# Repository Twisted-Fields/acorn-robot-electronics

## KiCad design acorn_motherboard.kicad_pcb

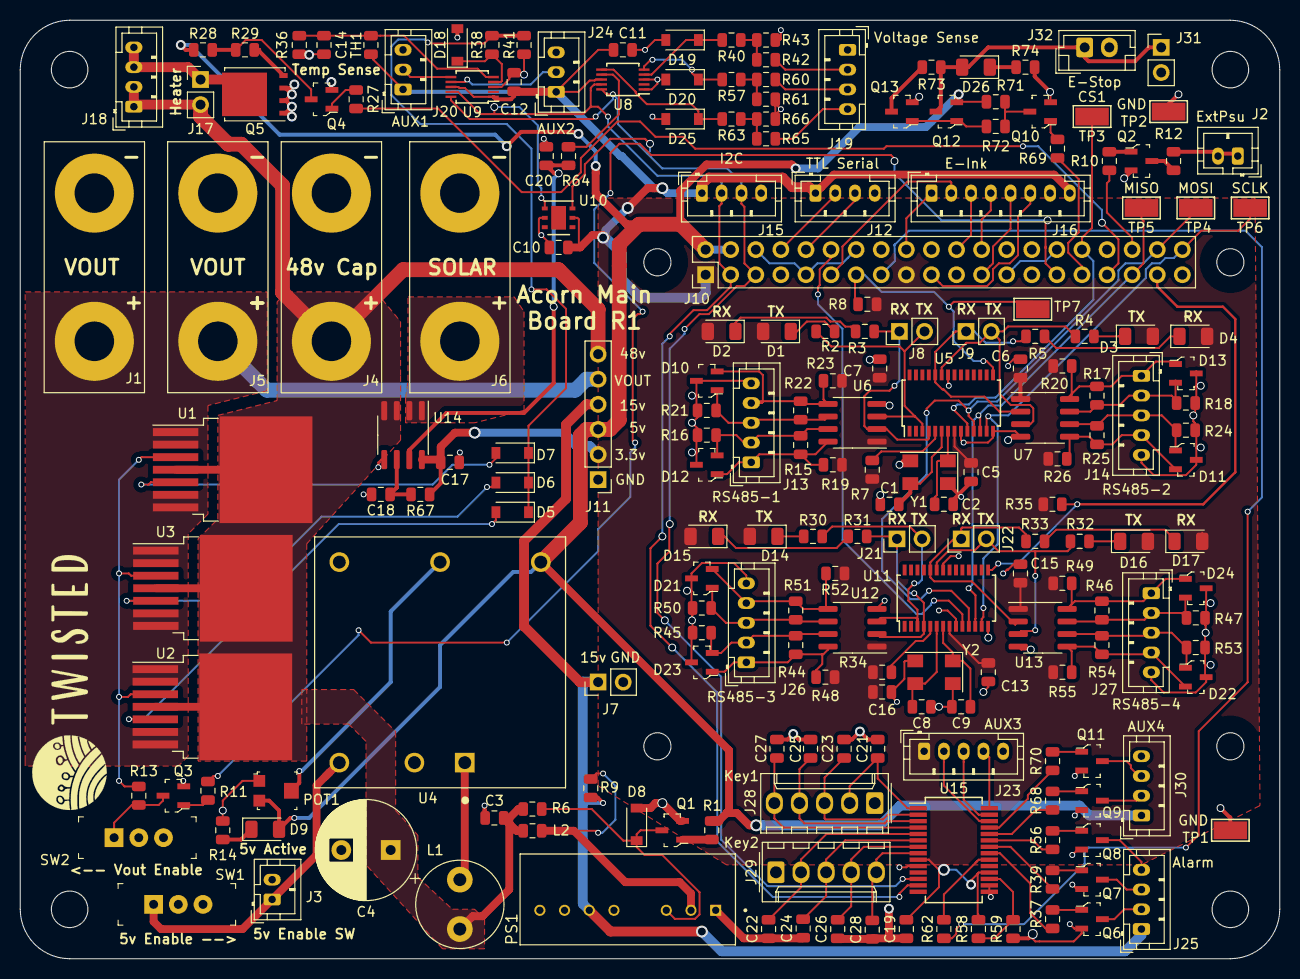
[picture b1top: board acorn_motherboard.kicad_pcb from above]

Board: 2 copper layers, 127.5 x 95.0 mm, 208 parts (0 on the bottom side), 138 nets.

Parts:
C1, C2, C8, C9: 18pF; C_0805_2012Metric
C3: 1uF 100v; C_0805_2012Metric
C4: CP; CP_Radial_D10.0mm_P5.00mm
C5, C6, C7, C10, C11, C12, C13, C14, C15, C16, C17, C19, C21, C22, C23, C24, C25, C26, C27, C28: 0.1uF; C_0805_2012Metric
C18: 1nF; C_0805_2012Metric
C20: 0.15uF; C_0805_2012Metric
D1, D2, D3, D4, D9, D14, D15, D16, D17, D26: LED; LED_1206_3216Metric
D5, D6, D7: D; D_SOD-123
D8: 12v Zener; D_SOD-123
D10, D11, D12, D13, D21, D22, D23, D24: CDSOT23-SM712; SOT-23-3
D18, D19, D20, D25: 3.3v Zener; D_SOD-123
H1, H2, H3, H4: MountingHole; MountingHole_3.7mm
J1, J4, J5, J6: Conn_01x02; BigWirePads
J2, J3: Conn_01x02; JST_PH_B2B-PH-K_1x02_P2.00mm_Vertical
J7, J8, J9, J17, J21, J22, J31: Conn_01x02; PinHeader_1x02_P2.54mm_Vertical
J10: RPi_GPIO; PinHeader_2x20_P2.54mm_Vertical
J11: Conn_01x06; PinHeader_1x06_P2.54mm_Vertical
J12, J15, J18, J19, J25, J30: Conn_01x04; JST_PH_B4B-PH-K_1x04_P2.00mm_Vertical
J13, J14, J23, J26, J27: Conn_01x05; JST_PH_B5B-PH-K_1x05_P2.00mm_Vertical
J16: Conn_01x08; JST_PH_B8B-PH-K_1x08_P2.00mm_Vertical
J20, J24: Conn_01x03; JST_PH_B3B-PH-K_1x03_P2.00mm_Vertical
J28, J29: Conn_01x05; Molex_KK-254_AE-6410-05A_1x05_P2.54mm_Vertical
J32: Conn_01x02; JST_EH_B2B-EH-A_1x02_P2.50mm_Vertical
L1: L; L_Radial_D8.7mm_P5.00mm_Fastron_07HCP
L2: 10uH; L_0805_2012Metric
POT1: TC33X-2-103E; Trimpot_3.8mmx3.6mm_TC33X-2-103E
PS1: SPBW06F-12; CONV_SPBW06F-12
Q1, Q2, Q3, Q4, Q6, Q7, Q8, Q9, Q10, Q11, Q13: 2N7002; SOT-23-3
Q5: FDMS8050; TDSON-8-1
Q12: AO3401A; SOT-23-3
R1, R10, R11, R12, R27, R29, R37, R39, R56, R68, R69, R70, R72, R73: 100R; R_0805_2012Metric
R2, R3, R4, R5, R30, R31, R32, R33: 500R; R_0805_2012Metric
R6, R28, R36, R38, R40, R57, R63, R64: 1k; R_0805_2012Metric
R7, R34, R42, R43, R59, R60, R61, R62, R65, R66: 10K; R_0805_2012Metric
R8, R35: 1K; R_0805_2012Metric
R9: 150pF; R_0805_2012Metric
R13, R41: 330R; R_0805_2012Metric
R14, R74: 220R; R_0805_2012Metric
R15, R17, R22, R25, R44, R46, R51, R54: 130R; R_0805_2012Metric
R16, R18, R19, R20, R21, R23, R24, R26, R45, R47, R48, R49, R50, R52, R53, R55: 750R; R_0805_2012Metric
R58: DNS; R_0805_2012Metric
R67: DNS for ACS725 / 0R for ACS722; R_0805_2012Metric
R71: 10k; R_0805_2012Metric
SW1, SW2: SW_SPDT; Switch_Slide_11.6x4mm_EG1218
TH1: Thermistor; R_0805_2012Metric
TP1, TP2, TP3, TP4, TP5, TP6, TP7: TestPoint; TestPoint_Keystone_5015_Micro-Minature
U1, U2, U3: BTS50085-1TMA; TO-263-7_TabPin4
U4: PDQ30-Q48-S5-D; CONV_PDQ30-Q48-S5-D
U5, U11: SC16IS752; TSSOP-28_4.4x9.7mm_P0.65mm
U6, U7, U12, U13: THVD1451D; SOIC-8_3.9x4.9mm_P1.27mm
U8, U9: ADS1115IDGS; TSSOP-10_3x3mm_P0.5mm
U10: HDC1080; Texas_PWSON-N6
U14: ACS725xLCTR-10AU; SOIC-8_3.9x4.9mm_P1.27mm
U15: MCP23017_SS; SSOP-28_5.3x10.2mm_P0.65mm
Y1, Y2: Crystal_GND24; Crystal_SMD_Abracon_ABM3C-4Pin_5.0x3.2mm

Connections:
15V_REMOTE: D8.1, PS1.3, Q1.3, R6.2
18VMAXIN: J19.2, R42.2
36VMAXIN: J19.3, R60.2
54VMAXIN: J19.4, R65.2
+3V3: C5.2, C6.1, C7.1, C10.1, C11.2, C12.2, C13.2, C15.1, C16.1, C17.2, C19.2, D1.2, D2.2, D3.2, D4.2, D14.2, D15.2, D16.2, D17.2, J10.1, J10.17, J11.2, J12.1, J15.1, J16.8, J20.1, J23.1, J24.1, R7.2, R8.2, R19.2, R20.2, R23.1, R26.1, R34.2, R35.2, R48.2, R49.2, R52.1, R55.1, R58.2, R67.1, TH1.1, U5.8, U6.1, U7.1, U8.8, U9.1, U9.8, U10.5, U11.8, U12.1, U13.1, U14.8, U15.9, U15.18
+5V: D9.2, J10.2, J10.4, J11.3, J30.1, POT1.3, Q12.2, R1.2, R28.1, R71.1, U4.3
+15V: J7.1, J11.4, J25.1, PS1.6, R9.1
+48V: C3.1, C4.1, J4.2, J11.6, J17.2, J18.1, J18.2, L1.2, L2.2, R6.1, U1.4, U2.4, U3.4, U14.3, U14.4
A1: D19.1, R40.2, U8.4
A2: D20.1, R57.2, U8.5
A3: D25.1, R63.2, U8.6
A4: R64.1, U8.7
A5: D18.1, R38.2, U9.4
A6: C14.1, R36.2, TH1.2, U9.5
A7: J20.2, U9.6
A8: J24.2, U9.7
CS1: J10.12, U11.10
CS2: J10.32, TP3.1, U5.10
EPD_BUSY: J10.18, J16.1
EPD_CS: J10.24, J16.4
EPD_DC: J10.22, J16.3
EPD_DIN: J10.19, J16.6
EPD_RESET: J10.11, J16.2
EPD_SCK: J10.23, J16.5
ESTOP: D26.2, J31.1, J32.1, Q12.3, R73.2
ESTOP_FET: J10.31, R69.1
EXT_PSU_ENABLE: J2.1, J2.2, R12.2
EXT_PSU_FET: J10.36, R10.1
GND: C1.1, C2.2, C3.2, C4.2, C5.1, C6.2, C7.2, C8.1, C9.2, C10.2, C11.1, C12.1, C13.1, C14.2, C15.2, C16.2, C17.1, C18.1, C19.1, C20.2, C21.1, C22.1, C23.1, C24.1, C25.1, C26.1, C27.1, C28.1, D8.2, D10.3, D11.3, D12.3, D13.3, D18.2, D19.2, D20.2, D21.3, D22.3, D23.3, D24.3, D25.2, J1.1, J3.2, J4.1, J5.1, J6.1, J7.2, J10.6, J10.9, J10.14, J10.20, J10.25, J10.30, J10.34, J10.39, J11.1, J12.4, J13.5, J14.5, J15.4, J16.7, J19.1, J20.3, J23.5, J24.3, J26.5, J27.5, J28.1, J29.1, J30.4, J31.2, J32.2, POT1.1, PS1.1, PS1.7, Q1.2, Q2.2, Q3.2, Q4.2, Q5.1, Q5.2, Q5.3, Q6.2, Q7.2, Q8.2, Q9.2, Q10.2, Q11.2, Q13.2, R14.2, R16.1, R18.1, R21.1, R24.1, R36.1, R41.2, R43.1, R45.1, R47.1, R50.1, R53.1, R59.1, R61.1, R66.1, R74.2, SW1.2, SW2.2, TP1.1, TP2.1, U4.2, U4.5, U5.9, U5.14, U5.22, U6.4, U7.4, U8.1, U8.3, U9.3, U10.2, U11.9, U11.14, U11.22, U12.4, U13.4, U14.5, U15.10, U15.15, U15.16, Y1.2, Y1.4, Y2.2, Y2.4
GP0: C21.2, J28.2, U15.1
GP1: C23.2, J28.3, U15.2
GP2: C25.2, J28.4, U15.3
GP3: C27.2, J28.5, U15.4
GP4: C22.2, J29.2, U15.5
GP5: C24.2, J29.3, U15.6
GP6: C26.2, J29.4, U15.7
GP7: C28.2, J29.5, U15.8
GP8: R37.1, U15.21
GP9: R39.1, U15.22
GP10: R56.1, U15.23
GP11: R68.1, U15.24
GP12: R70.1, U15.25
GP13: J23.2, U15.26
GP14: J23.3, U15.27
GP15: J23.4, U15.28
GPIO_INT: J10.15, R62.1
IRQ1: J10.37, R35.1, U11.15
IRQ2: J10.13, R8.1, TP7.1, U5.15
MISO: J10.35, TP5.1, U5.12, U11.12
MOSI: J10.38, TP4.1, U5.11, U11.11
unnamed: C1.2, U5.6, Y1.3
unnamed: C2.1, U5.7, Y1.1
unnamed: C8.2, U11.6, Y2.3
unnamed: C9.1, U11.7, Y2.1
unnamed: C18.2, R67.2, U14.6
unnamed: C20.1, R64.2, U14.7
unnamed: D1.1, R2.1
unnamed: D2.1, R3.1
unnamed: D3.1, R4.1
unnamed: D4.1, R5.1
unnamed: D5.2, U2.5
unnamed: D6.2, U3.5
unnamed: D7.2, U1.5
unnamed: D9.1, R14.1
unnamed: D10.1, J13.3, R21.2, R22.2, U6.6
unnamed: D10.2, J13.4, R22.1, R23.2, U6.5
unnamed: D11.1, J14.3, R24.2, R25.2, U7.6
unnamed: D11.2, J14.4, R25.1, R26.2, U7.5
unnamed: D12.1, J13.1, R15.2, R19.1, U6.8
unnamed: D12.2, J13.2, R15.1, R16.2, U6.7
unnamed: D13.1, J14.1, R17.2, R20.1, U7.8
unnamed: D13.2, J14.2, R17.1, R18.2, U7.7
unnamed: D14.1, R30.1
unnamed: D15.1, R31.1
unnamed: D16.1, R32.1
unnamed: D17.1, R33.1
unnamed: D21.1, J26.3, R50.2, R51.2, U12.6
unnamed: D21.2, J26.4, R51.1, R52.2, U12.5
unnamed: D22.1, J27.3, R53.2, R54.2, U13.6
unnamed: D22.2, J27.4, R54.1, R55.2, U13.5
unnamed: D23.1, J26.1, R44.2, R48.1, U12.8
unnamed: D23.2, J26.2, R44.1, R45.2, U12.7
unnamed: D24.1, J27.1, R46.2, R49.1, U13.8
unnamed: D24.2, J27.2, R46.1, R47.2, U13.7
unnamed: D26.1, R74.1
unnamed: J3.1, SW1.1, U4.6
unnamed: J17.1, J18.3, J18.4, Q5.5
unnamed: J25.2, Q6.3
unnamed: J25.3, Q7.3
unnamed: J25.4, Q8.3
unnamed: J30.2, Q9.3
unnamed: J30.3, Q11.3
unnamed: L1.1, U4.1
unnamed: L2.1, PS1.2, R9.2
unnamed: POT1.2, U4.4
unnamed: Q1.1, R1.1
unnamed: Q2.1, R10.2
unnamed: Q2.3, R12.1
unnamed: Q3.1, R11.2
unnamed: Q3.3, R13.1, SW2.1
unnamed: Q4.1, R27.2
unnamed: Q4.3, R28.2, R29.1
unnamed: Q5.4, R29.2
unnamed: Q6.1, R37.2
unnamed: Q7.1, R39.2
unnamed: Q8.1, R56.2
unnamed: Q9.1, R68.2
unnamed: Q10.1, R69.2
unnamed: Q10.3, R71.2, R72.2
unnamed: Q11.1, R70.2
unnamed: Q12.1, Q13.1, R72.1
unnamed: Q13.3, R73.1
unnamed: R7.1, U5.5
unnamed: R34.1, U11.5
unnamed: R40.1, R42.1, R43.2
unnamed: R57.1, R60.1, R61.2
unnamed: R58.1, R59.2, U15.17
unnamed: R62.2, U15.20
unnamed: R63.1, R65.1, R66.2
PWM_HEATER: J10.33, R27.1
RX: J10.10, J12.3
RX1: J21.1, R31.2, U11.4, U12.2
RX2: J22.1, R33.2, U11.24, U13.2
RX3: J8.1, R3.2, U5.4, U6.2
RX4: J9.1, R5.2, U5.24, U7.2
SCL: J10.5, J15.3, U8.10, U9.10, U10.6, U15.12
SCLK: J10.40, TP6.1, U5.13, U11.13
SDA: J10.3, J15.2, U8.9, U9.9, U10.1, U15.13
SOLARIN: J6.2, U14.1, U14.2
TX: J10.8, J12.2
TX1: J21.2, R30.2, U11.3, U12.3
TX2: J22.2, R32.2, U11.23, U13.3
TX3: J8.2, R2.2, U5.3, U6.3
TX4: J9.2, R4.2, U5.23, U7.3
VOUT: J1.2, J5.2, J11.5, U1.1, U1.2, U1.6, U1.7, U2.1, U2.2, U2.6, U2.7, U3.1, U3.2, U3.6, U3.7
VOUT_FET: J10.29, R11.1
VOUT_ISENSE: D5.1, D6.1, D7.1, R38.1, R41.1
|VOUT_ENABLE|: R13.2, U1.3, U2.3, U3.3

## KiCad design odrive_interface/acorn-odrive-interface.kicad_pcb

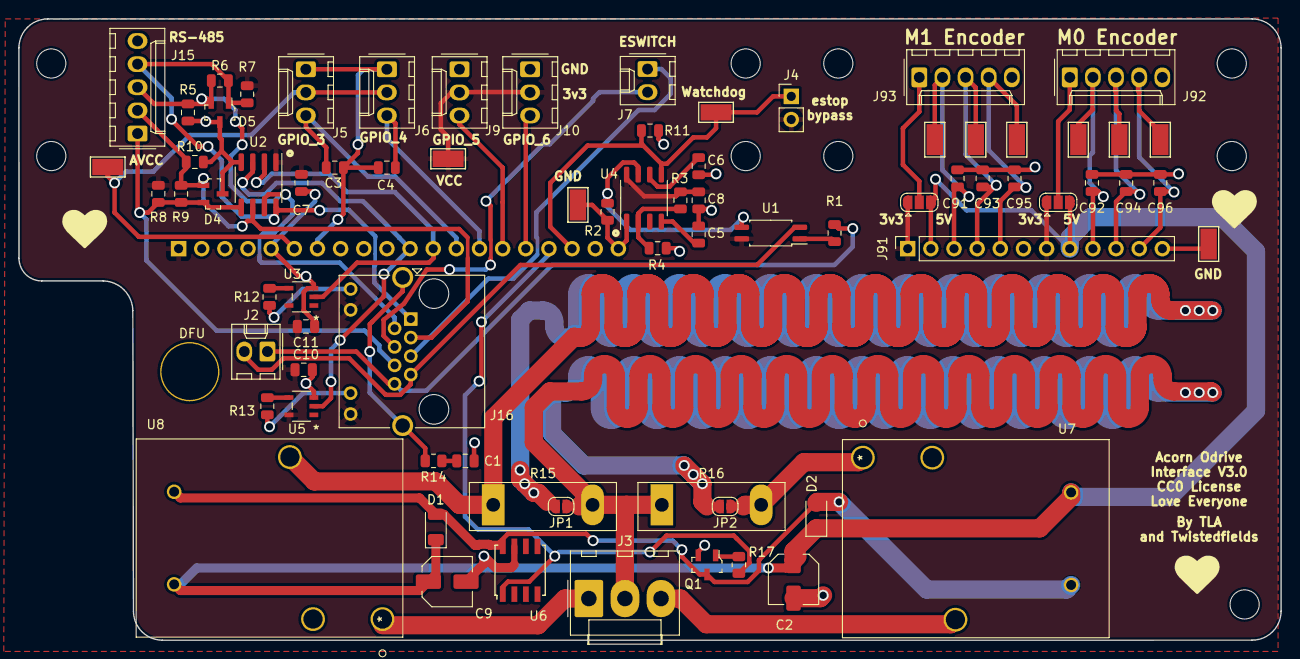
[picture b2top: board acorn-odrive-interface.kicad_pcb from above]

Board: 2 copper layers, 138.5 x 68.2 mm, 86 parts (1 on the bottom side), 47 nets.

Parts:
C1, C7, C8, C10, C11: 0.1uF; C_0805_2012Metric
C2, C9: 10uF; C_Elec_5x5.4
C3, C4: DNP; C_0805_2012Metric
C5, C6: 3900pF NP0; C_0805_2012Metric
C91, C92, C93, C94, C95, C96: 47pF; C_0805_2012Metric
D1, D2: D; D_1206_3216Metric
D4, D5: CDSOT23-SM712; SOT-23-3
H1, H2, H3, H4, H5, H91, H92, H93, H94: MountingHole; MountingHole_3.2mm_M3
H9: MountingHole; MountingHole_6.4mm_M6
J1: Conn_01x20_Male; PinHeader_1x20_P2.54mm_Vertical
J2: DNP; Molex_KK-254_AE-6410-02A_1x02_P2.54mm_Vertical
J3: DNP; Molex_KK-396_A-41791-0003_1x03_P3.96mm_Vertical
J4: Conn_01x02; PinHeader_1x02_P2.54mm_Vertical
J5, J6, J9, J10: Conn_01x03; Molex_KK-254_AE-6410-03A_1x03_P2.54mm_Vertical
J7: Conn_01x02; Molex_KK-254_AE-6410-02A_1x02_P2.54mm_Vertical
J15: Conn_01x05; Molex_KK-254_AE-6410-05A_1x05_P2.54mm_Vertical
J16: RJ45_LED_Shielded; RJ45_Amphenol_RJHSE538X
J91: Conn_01x12_Female; PinSocket_1x12_P2.54mm_Vertical
J92, J93: Conn_01x05_Male; Molex_KK-254_AE-6410-05A_1x05_P2.54mm_Vertical
JP1, JP2: SolderJumper_2_Open; SolderJumper-2_P1.3mm_Open_RoundedPad1.0x1.5mm
JP91, JP92: SolderJumper_3_Bridged12; SolderJumper-3_P1.3mm_Open_RoundedPad1.0x1.5mm
Q1: DNP; SOT-23-3
R1: 220R; R_0805_2012Metric
R2, R11: 10k; R_0805_2012Metric
R3, R4: 1M; R_0805_2012Metric
R5, R7, R8, R10: 750R; R_0805_2012Metric
R6, R9: 130R; R_0805_2012Metric
R12, R13, R14: 470R; R_0805_2012Metric
R15, R16: DNP; TO-247-2_Vertical
R17: 100R; R_0805_2012Metric
TP1, TP2, TP4, TP5, TP91, TP92, TP93, TP94, TP95, TP96, TP97: TestPoint; TestPoint_Keystone_5015_Micro-Minature
U1: PS2805A-1-A; SOP-4_4.4x2.6mm_P1.27mm
U2: THVD1451D; SOIC-8_3.9x4.9mm_P1.27mm
U3, U5: buffer; SN74LVC1G07QDCKTQ1
U4: UCC2946D; SO-8_3.9x4.9mm_P1.27mm
U6: BV1LC105FJ-C; SOJ-8_6x4mm_P1.27mm
U7, U8: 1558667-1

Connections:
3v3: C7.1, C8.1, C10.1, C11.1, J1.1, J4.2, J9.2, J10.2, J16.10, J16.12, J91.1, J91.7, JP91.1 (A), JP92.1 (A), R3.2, R7.2, R8.1, TP1.1, U1.4, U2.1 (VCC), U3.5 (VCC), U4.8 (VDD), U5.5 (VCC)
5V: C2.1, C9.1, D1.1 (K), D2.1 (K), J91.2, J91.8, JP91.3 (B), JP92.3 (B), U7.4, U8.4
/Enc1PosV: J93.1, JP92.2 (C)
AGND: C3.2, C4.2, J1.7, J5.1, J6.1
AVCC: J1.6, J5.2, J6.2, TP5.1
COIL_DRIVE: D1.2 (A), D2.2 (A), Q1.3 (D), U6.8 (OUT1), U7.5, U8.5
E1: J2.1, J16.8, R1.1
E2: J2.2, J16.7, U1.2
E_SWITCH1: J7.1, J16.5
E_SWITCH2: J7.2, J16.4
Enc0A: C92.1, J91.9, J92.2, TP95.1
Enc0B: C94.1, J91.10, J92.3, TP96.1
Enc0Z: C96.1, J91.11, J92.4, TP97.1
Enc1A: C91.1, J91.3, J93.2, TP92.1
Enc1B: C93.1, J91.4, J93.3, TP93.1
Enc1Z: C95.1, J91.5, J93.4, TP94.1
GND: C1.1, C2.2, C5.2, C6.2, C7.2, C8.2, C9.2, C10.2, C11.2, C91.2, C92.2, C93.2, C94.2, C95.2, C96.2, D4.3 (Output), D5.3 (Output), J1.2, J1.5, J1.19, J1.20, J9.1, J10.1, J15.5, J91.6, J91.12, J92.5, J93.5, Q1.2 (S), R2.2, R4.1, R5.1, R10.1, R11.2, TP4.1, TP91.1, U2.4 (GND), U3.3 (GND), U4.1 (GND), U5.3 (GND), U6.7 (GND)
GPIO_1: J1.11, U2.3 (D), U5.2 (A)
GPIO_2: J1.12, U2.2 (R), U3.2 (A)
GPIO_3: C3.1, J1.13, J5.3
GPIO_4: C4.1, J1.14, J6.3
GPIO_5: J1.15, J9.3
GPIO_6: J1.16, J10.3
GPIO_7: J1.17, R17.2, U6.1 (IN)
GPIO_8: J1.18, J4.1, R11.1, TP2.1, U4.5 (*WDO)
unnamed: C1.2, R14.2
unnamed: C5.1, U4.4 (RP)
unnamed: C6.1, U4.6 (WP)
unnamed: D4.1 (Input), J15.2, J16.3, R9.2, R10.2, U2.6 (Z)
unnamed: D4.2 (Input), J15.1, J16.6, R8.2, R9.1, U2.5 (Y)
unnamed: D5.1 (Input), J15.4, J16.1, R6.2, R7.1, U2.8 (A)
unnamed: D5.2 (Input), J15.3, J16.2, R5.2, R6.1, U2.7 (B)
unnamed: J3.1, U8.1
unnamed: J3.2, JP1.1 (A), JP2.2 (B), R15.2, R16.1
unnamed: J3.3, U7.3
unnamed: J16.9, R12.2
unnamed: J16.11, R13.2
unnamed: J16.SH, R14.1
unnamed: J92.1, JP91.2 (C)
unnamed: JP1.2 (B), R15.1, U8.3
unnamed: JP2.1 (A), R16.2, U7.1
unnamed: Q1.1 (G), R17.1
unnamed: R1.2, U1.1
unnamed: R3.1, R4.2, U4.2 (RTH)
WDI: R2.1, U1.3, U4.7 (WDI)
led_buffer_rx: R12.1, U3.4 (Y)
led_buffer_tx: R13.1, U5.4 (Y)

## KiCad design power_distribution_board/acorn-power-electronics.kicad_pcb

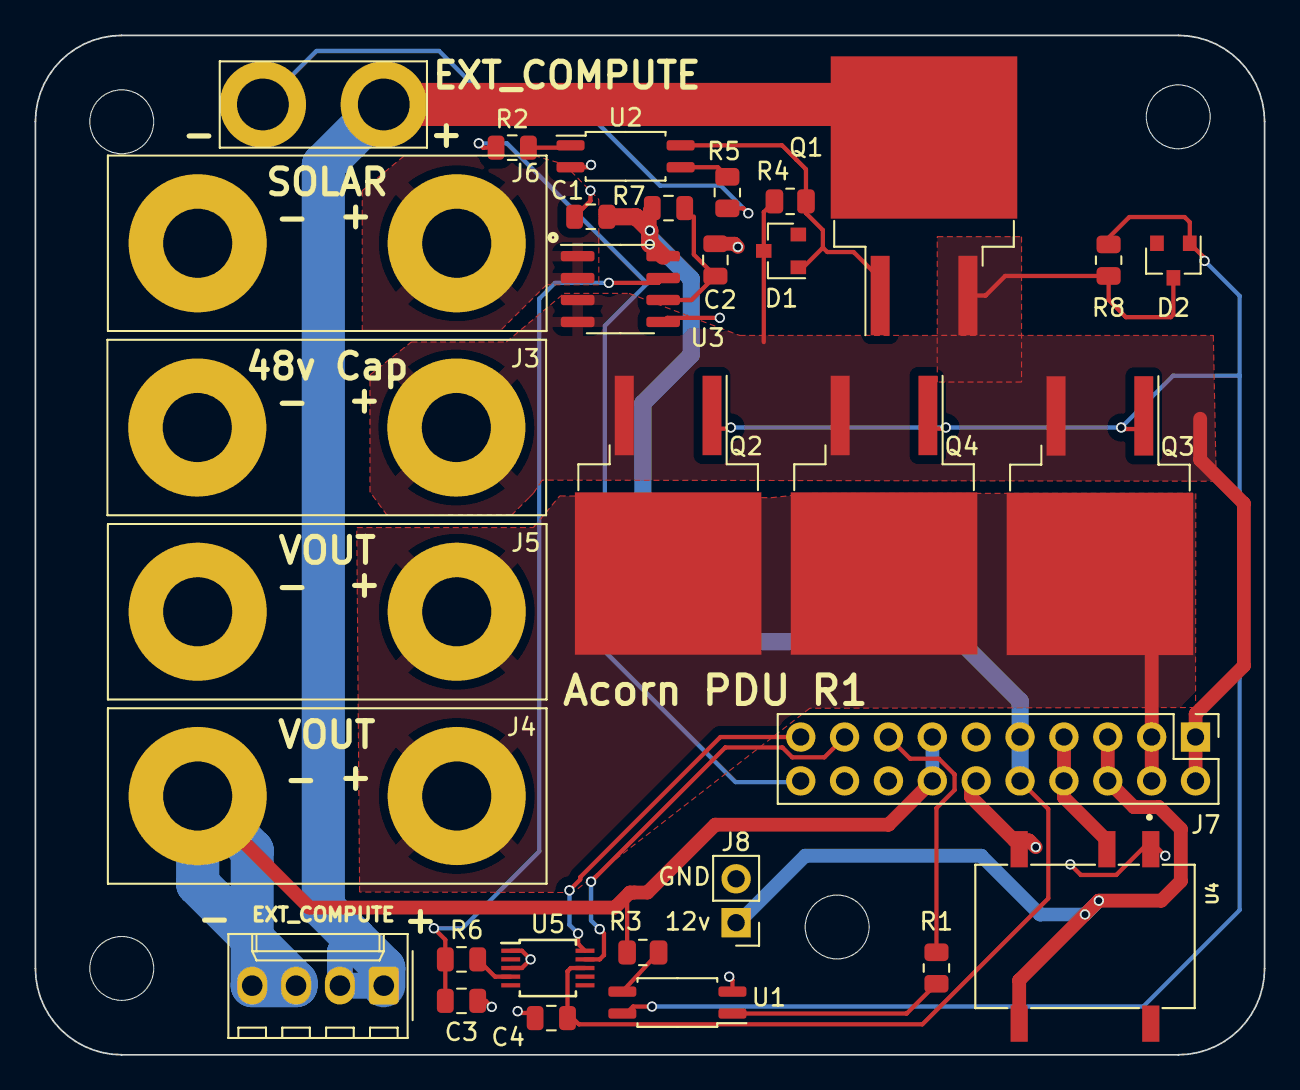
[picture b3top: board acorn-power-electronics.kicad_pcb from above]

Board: 2 copper layers, 71.2 x 59.0 mm, 35 parts (0 on the bottom side), 22 nets.

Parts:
C1, C4: 0.1uF; C_0805_2012Metric
C2: 1000pF; C_0805_2012Metric
C3: 0.15uF; C_0805_2012Metric
D1, D2: BZX84Cxx; D_SOT-23_ANK
H1, H2, H3, H4: MountingHole; MountingHole_3.7mm
J1: Conn_01x04; Molex_KK-254_AE-6410-04A_1x04_P2.54mm_Vertical
J2: Conn_01x02; medium_big_pads
J3, J4, J5, J6: Conn_01x02; BigWirePads
J7: Conn_02x10_Counter_Clockwise; PinHeader_2x10_P2.54mm_Vertical
J8: Conn_01x02; PinHeader_1x02_P2.54mm_Vertical
Q1, Q2, Q3, Q4: IXTA96P085T-TRL; TO-263-2-pad4
R1, R2: 330R; R_0805_2012Metric
R3, R5: 200; R_0805_2012Metric
R4, R6, R8: 1k; R_0805_2012Metric
R7: DNS for ACS725 / 0R for ACS722; R_0805_2012Metric
U1, U2: ACPL-214-500E; SOP-4_4.4x2.6mm_P1.27mm
U3: ACS725xLCTR-10AU; SOIC-8_3.9x4.9mm_P1.27mm
U4: PDS1-S5-S12-M-TR; CONV_PDS1-S3-S3-M
U5: ADS1115IDGS; TSSOP-10_3x3mm_P0.5mm

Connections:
+3V3: C1.2, C4.2, J7.9, J7.10, R7.1, U3.8 (VCC), U5.8 (VDD)
+5V: J7.7, J7.8, U4.2 (VIN)
+12V: J7.5, J7.6, J8.1, U4.5 (+VO)
+48V: D1.1 (K), D2.1 (K), J3.2, J7.1, J7.2, Q1.3 (S), Q2.3 (S), Q3.3 (S), Q4.3 (S), R4.2, R8.2, U3.3 (IP-), U3.4 (IP-)
A1: R6.1, U5.4 (AIN0)
EXT_PSU_FET: J7.20, R2.1
GND: C1.1, C2.1, C3.2, C4.1, J7.11, J7.12, J8.2, U1.2, U2.2, U3.5 (GND), U4.1 (GND), U4.4 (0V), U5.1 (ADDR), U5.3 (GND)
GNDPWR: J1.3, J1.4, J2.2, J3.1, J4.1, J5.1, J6.1, J7.13, J7.14, R3.1, R5.1
unnamed: C2.2, R7.2, U3.6 (FILTER)
unnamed: C3.1, R6.2, U3.7 (VIOUT)
unnamed: D1.2 (A), Q1.1 (G), R4.1, U2.4
unnamed: R1.2, U1.1
unnamed: R2.2, U2.1
unnamed: R3.2, U1.3
unnamed: R5.2, U2.3
SCL: J7.19, U5.10 (SCL)
SDA: J7.17, U5.9 (SDA)
SOLARIN: J6.2, U3.1 (IP+), U3.2 (IP+)
VOUT: J4.2, J5.2, J7.3, J7.4, Q2.4 (D), Q3.4 (D), Q4.4 (D)
VOUT_ENABLE: J7.15, R1.1
VOUT_EXT_COMPUTE: J1.1, J1.2, J2.1, Q1.4 (D)
VOUT_FET: D2.2 (A), Q2.1 (G), Q3.1 (G), Q4.1 (G), R8.1, U1.4

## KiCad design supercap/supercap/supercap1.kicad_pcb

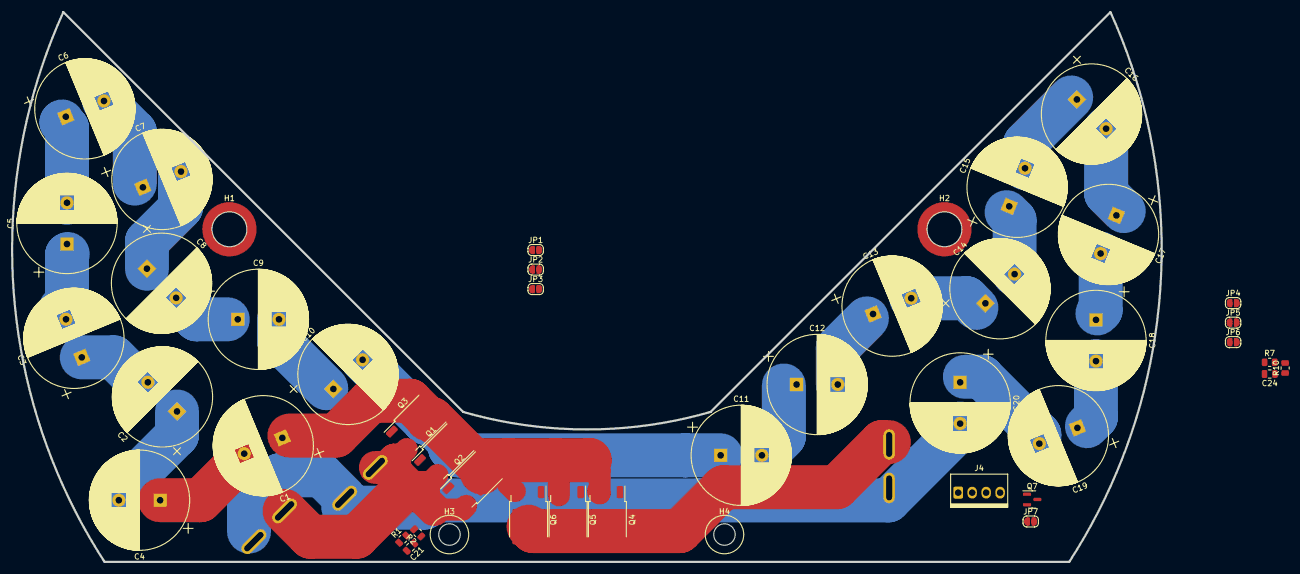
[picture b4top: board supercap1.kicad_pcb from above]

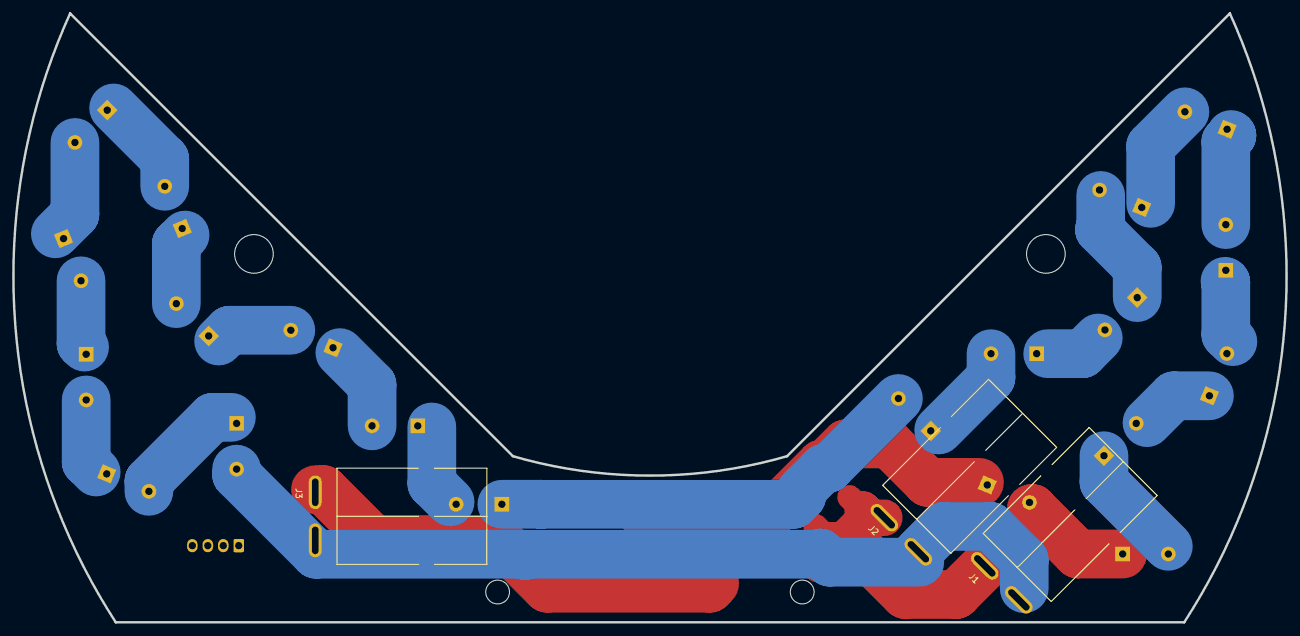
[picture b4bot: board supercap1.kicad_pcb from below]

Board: 2 copper layers, 209.0 x 100.0 mm, 48 parts (3 on the bottom side), 27 nets.

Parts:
C1, C2, C3, C4, C5, C6, C7, C8, C9, C10, C11, C12, C13, C14, C15, C16, C17, C18, C19, C20: 120F 2.3v; CP_Radial_D18.0mm_P7.50mm
C21, C24: 1uF; C_0805_2012Metric
H1, H2: MountingHole_Pad; Sinhoo-SMTSO40x-C2916378
H3, H4: MountingHole; MountingHole_3.9mm_Plastite_#6
J1, J2: Conn_01x02; PowerPole_PP45_1336G1_1x2_Horizontal
J3: Power Output; PowerPole_PP45_1336G1_1x2_Horizontal
J4: CAN2 PLUG; PINREX-744-81-04TW00 _1x04_P2.54mm_Vertical
JP1, JP2, JP3, JP4, JP5, JP6, JP7: SolderJumper_2_Open; SolderJumper-2_P1.3mm_Open_RoundedPad1.0x1.5mm
Q1, Q2, Q3, Q4, Q5, Q6: 100V 34A PMOS; TO-252-2
Q7: Q_NMOS_GSD; SOT-23
R1, R7: 10k; R_0805_2012Metric
R2, R10: 20k; R_0805_2012Metric

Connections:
+5V: J4.1, Q7.1 (G)
/VBUS_GATE: C21.1, Q1.1 (G), Q2.1 (G), Q3.1 (G), R1.2, R2.1
/VCAP_GATE: C24.1, Q4.1 (G), Q5.1 (G), Q6.1 (G), R7.2, R10.1
GND: C20.2, J1.2, J2.2, J3.2, J4.4, JP7.2 (B), Q7.2 (S), R2.2
unnamed: C1.2, C4.1
unnamed: C2.1, C4.2
unnamed: C2.2, C3.1
unnamed: C3.2, C5.1
unnamed: C5.2, C6.1
unnamed: C6.2, C7.1
unnamed: C7.2, C8.1
unnamed: C8.2, C9.1
unnamed: C9.2, C10.1
unnamed: C10.2, C11.1
unnamed: C11.2, C12.1
unnamed: C12.2, C13.1
unnamed: C13.2, C14.1
unnamed: C14.2, C15.1
unnamed: C15.2, C16.1
unnamed: C16.2, C17.1
unnamed: C17.2, C18.1
unnamed: C18.2, C19.1
unnamed: C19.2, C20.1
unnamed: JP7.1 (A), Q7.3 (D), R10.2
VBUS: C21.2, J1.1, J2.1, JP1.1 (A), JP2.1 (A), JP3.1 (A), Q1.3 (S), Q2.3 (S), Q3.3 (S), R1.1
VCAP: C1.1, C24.2, JP1.2 (B), JP2.2 (B), JP3.2 (B), JP4.1 (A), JP5.1 (A), JP6.1 (A), Q1.2 (D), Q2.2 (D), Q3.2 (D), Q4.3 (S), Q5.3 (S), Q6.3 (S), R7.1
VOUT: J3.1, JP4.2 (B), JP5.2 (B), JP6.2 (B), Q4.2 (D), Q5.2 (D), Q6.2 (D)

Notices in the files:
odrive_interface/acorn-odrive-interface.kicad_pcb:
CC0 License
Design licensed CC0 - Public Domain. Use this information for any purpose.
parts and their libraries:
Copyright 2021 Accelerated Designs. All rights reserved.
